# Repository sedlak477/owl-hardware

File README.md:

# OWL Hardware

Hardware design files for the OWL measurement tool.

The OWL is a rotating platform driven by a BLDC motor under field-oriented control.
Power and USB data are passed from the stationary base to the rotating part through a slip ring,
so devices mounted on top can be rotated continuously while staying connected to a host.

## Status

- **[v1.0.0](https://github.com/sedlak477/owl-hardware/releases/tag/v1.0.0)** is the OWL as built and tested. It works, with the known issues listed in its release notes:
  the 5V rail can oscillate when USB and the power supply are both connected (workaround: cut the controller's `VBUS` jumper JP1),
  the stator's data USB-C port only works in one cable orientation,
  the sensor's mounting holes are missing (drill them, 1.8 mm),
  the green LEDs are very bright,
  and the USB hub (IC1) has no pin-1 marker.
- **Releases after v1.0.0**, including the latest, should fix these issues, but no boards have been built from them yet, so they are **untested**.
  Other changes since the built boards: plated shell-tab holes for the controller's USB-C connector J3, a different part for the controller's `USER` LED D7, and no assembled parts on the controller's bottom side.
- The payload adapters and the tripod mount in [`payload/`](payload/README.md) use version 2 of the payload connector, which is incompatible with version 1. For an OWL with the version 1 connector, use [release v1.2.2](https://github.com/sedlak477/owl-hardware/tree/v1.2.2).
- The 5V oscillation is only worked around: JP1 now ships open, so the controller runs from the power supply only (see [Power supply](docs/Assembly%20instructions.md#power-supply)). A proper fix is planned for the next board revision.

## Building an OWL

1. Download the files from the [latest release](https://github.com/sedlak477/owl-hardware/releases/latest):
   - `owl-<version>-jlcpcb.zip`: everything needed to order the three assembled PCBs from JLCPCB
   - `owl-<version>-3d-print.zip`: the 3D-printed parts
   - `owl-<version>-generic.zip`: manufacturer-neutral PCB files and schematics, if you order elsewhere
2. Order the PCBs, see [pcb/README.md](pcb/README.md).
3. Print the parts, see [cad/README.md](cad/README.md).
4. Assemble the OWL and flash the firmware, see the [assembly instructions](docs/Assembly%20instructions.md).
5. Print an adapter for your payload, see [payload/README.md](payload/README.md).

## Architecture

- **Stator PCB**: Sits in the stationary base. Provides the USB-C power input with a USB PD trigger (CH224K) and the USB data port to the host.
- **Rotor PCB** (controller): Rotates with the platform. Contains the RP2354B controller, the DRV8311 BLDC driver, 5 V and 3.3 V regulators, a USB hub with a passthrough port for the payload, and a Qwiic (I²C) port.
- **Magnetic sensor PCB**: Measures the rotor angle for motor control using a magnetic angle sensor.

## Repository structure

| Path             | Content                                         |
| :--------------- | :---------------------------------------------- |
| `pcb/controller` | KiCad project for the rotor/controller PCB.     |
| `pcb/stator`     | KiCad project for the stator PCB.               |
| `pcb/sensor`     | KiCad projects for the magnetic sensor PCBs.    |
| `cad`            | Link to the Onshape document and 3D-print files.|
| `payload`        | Adapters for mounting payloads, and the payload interface. |
| `docs`           | Assembly instructions, renders, and diagrams.   |

Each PCB folder contains a `schematic.pdf`, the KiCad project in `src`, and production files in `production` (generic, and ready to upload to JLCPCB). See [pcb/README.md](pcb/README.md) for the stackups and how to order the boards.

## Editing the design

Requirements:

- [KiCad](https://www.kicad.org/) 10 or newer
- [Git LFS](https://git-lfs.com/) for STEP models, PDFs, images, and fabrication archives

```sh
git lfs install
git clone git@github.com:sedlak477/owl-hardware.git
```

After changing a board, regenerate its production files with `pcb/export-production.sh` (see [pcb/README.md](pcb/README.md#regenerating-the-production-files-only-after-changing-the-design)).
Pushing a tag starting with `v` (e.g. `v1.1.0`) creates a release with the packaged production and 3D-print files.

## Related resources

[owl-firmware](https://github.com/sedlak477/owl-firmware): The firmware for the OWL platform.  
[owl-ranger](https://github.com/sedlak477/owl-ranger): A script for stepping through some orientations and recording measurements.  
[pyowl](https://github.com/sedlak477/pyowl): A python library for interacting with the OWL.  
[Dataset](https://doi.org/10.3217/kh254-z8374): Orientation-diverse BLE Channel Sounding and UWB ranging measurements recorded with the OWL.

## License

Copyright 2026 Michael Sedlak. Licensed under [CERN-OHL-P-2.0](LICENSE), without any warranty.

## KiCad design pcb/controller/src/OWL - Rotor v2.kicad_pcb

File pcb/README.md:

# PCBs

| Board                         | Folder             | Layers | Size           | Thickness | Copper                    | Solder mask | Parts on    |
| :---------------------------- | :----------------- | :----- | :------------- | :-------- | :------------------------ | :---------- | :---------- |
| Rotor / controller            | `controller/`      | 4      | 60 x 60 mm     | 1.6 mm    | 1 oz outer, 0.5 oz inner  | Purple      | top only    |
| Stator                        | `stator/`          | 2      | 44 x 44 mm     | 1.6 mm    | 1 oz                      | Black       | both sides  |
| Magnetic sensor (MA600A)      | `sensor/ma600a/`   | 2      | 22.3 x 20 mm   | 1.6 mm    | 1 oz                      | Yellow      | both sides  |

ENIG surface finish is recommended.
Minimum track width and clearance are 0.15 mm, minimum drill is 0.25 mm (controller) or 0.3 mm (stator, sensor).

Each board folder contains:

| Path                  | Content                                                                          |
| :-------------------- | :------------------------------------------------------------------------------- |
| `schematic.pdf`       | Schematic.                                                                       |
| `src/`                | KiCad project and STEP model of the assembled board.                             |
| `production/generic/` | Files for any manufacturer (see below).                                          |
| `production/jlcpcb/`  | Files ready to upload to JLCPCB for fabrication and assembly.                    |

The easiest way to get the files is the [latest release](https://github.com/sedlak477/owl-hardware/releases/latest): `owl-<version>-jlcpcb.zip` has the JLCPCB files and `owl-<version>-generic.zip` the generic files and schematics, each with one folder per board.

## Ordering from JLCPCB

> [!WARNING]
> **Check the rotation of every part in JLCPCB's placement preview before you order.**
> JLCPCB's part models don't always line up with the footprints, so some parts can show up rotated (often by 90° or 180°) or shifted.
> JLCPCB assembles the board as the preview shows it: a wrongly rotated IC, LED or connector is soldered on the wrong way round, and the board has to be reworked or thrown away.
> See step 5 below.

Order each board (`controller`, `stator`, `sensor-ma600a`) separately. Download and unzip `owl-<version>-jlcpcb.zip`, then for each board:

1. Go to [jlcpcb.com](https://jlcpcb.com), click *Order now*, and upload `<board>/<board>-gerbers.zip`. Don't unzip it, JLCPCB wants the zip.
2. Check that layers, size and thickness match the table above, and pick the solder mask color you like.
3. Enable *PCB Assembly*. The controller is assembled on the top side only; the stator and the sensor have parts on both sides, so select assembly on both sides for them.
4. Upload `<board>/<board>-bom.csv` as the BOM and `<board>/<board>-positions.csv` as the CPL (pick-and-place) file.
5. Check the part matching, then go through **every part** in the placement preview and check both its position and its rotation:
   - Position: its pins sit on their pads.
   - Rotation of ICs: the pin-1 marker on the part (dot, notch or bevel) sits at the pin-1 marker on the silkscreen.
   - Rotation of LEDs: the cathode sits at the cathode marker on the silkscreen.
   - Rotation of connectors: the part matches its silkscreen outline, with the opening on the correct side.

   Rotate or move any part that is off directly in the preview before ordering. Resistors and ceramic capacitors are not polarized, so for them a 180° rotation does not matter.

On the controller, the optional RM2 radio module (U6) and microSD socket (J8) are marked DNP and are not assembled, and neither are their support parts on the bottom side (C43, C44, R1, R2). Solder them by hand if you need them; their values and part numbers are in the schematic.

## Ordering elsewhere

`owl-<version>-generic.zip` (or `production/generic/` in each board folder) contains manufacturer-neutral files, plus each board's schematic:

| File                      | Content                                                                                       |
| :------------------------ | :-------------------------------------------------------------------------------------------- |
| `<board>-gerbers.zip`     | Gerber X2 layers, Excellon drill files (plated and non-plated separate), and a Gerber job file with the stackup. |
| `<board>-netlist.ipc`     | IPC-D-356 netlist for electrical testing.                                                     |
| `<board>-bom.csv`         | BOM with manufacturer and manufacturer part number (MPN), plus the LCSC number where available. |
| `<board>-positions.csv`   | Pick-and-place file as exported by KiCad (mm, rotation in KiCad convention, both sides).      |

The Gerbers work at any PCB manufacturer.
Assembly houses usually want the BOM and position files in their own format; the columns in the generic files map directly to theirs.
Rotation conventions differ between assembly houses, so **check the rotation of every polarized part in their placement preview**, the same way as for JLCPCB (step 5 above).
The JLCPCB position file is not generic: it contains JLCPCB-specific rotation and offset corrections.

## Regenerating the production files (only after changing the design)

Not needed for ordering boards: the production files in each release are ready to use.

Run `pcb/export-production.sh` (or `pcb/export-production.sh <board>` for one board: `controller`, `stator`, `sensor-ma600a`).
It needs `kicad-cli` (KiCad 10) and, for the JLCPCB files, the [Fabrication Toolkit](https://github.com/bennymeg/Fabrication-Toolkit) KiCad plugin.
Set `KICAD_PYTHON` to the Python interpreter KiCad uses if it is not the default `python3`, and `FABRICATION_TOOLKIT_DIR` if the plugin is not installed in `~/.local/share/kicad/10.0/3rdparty/plugins`.

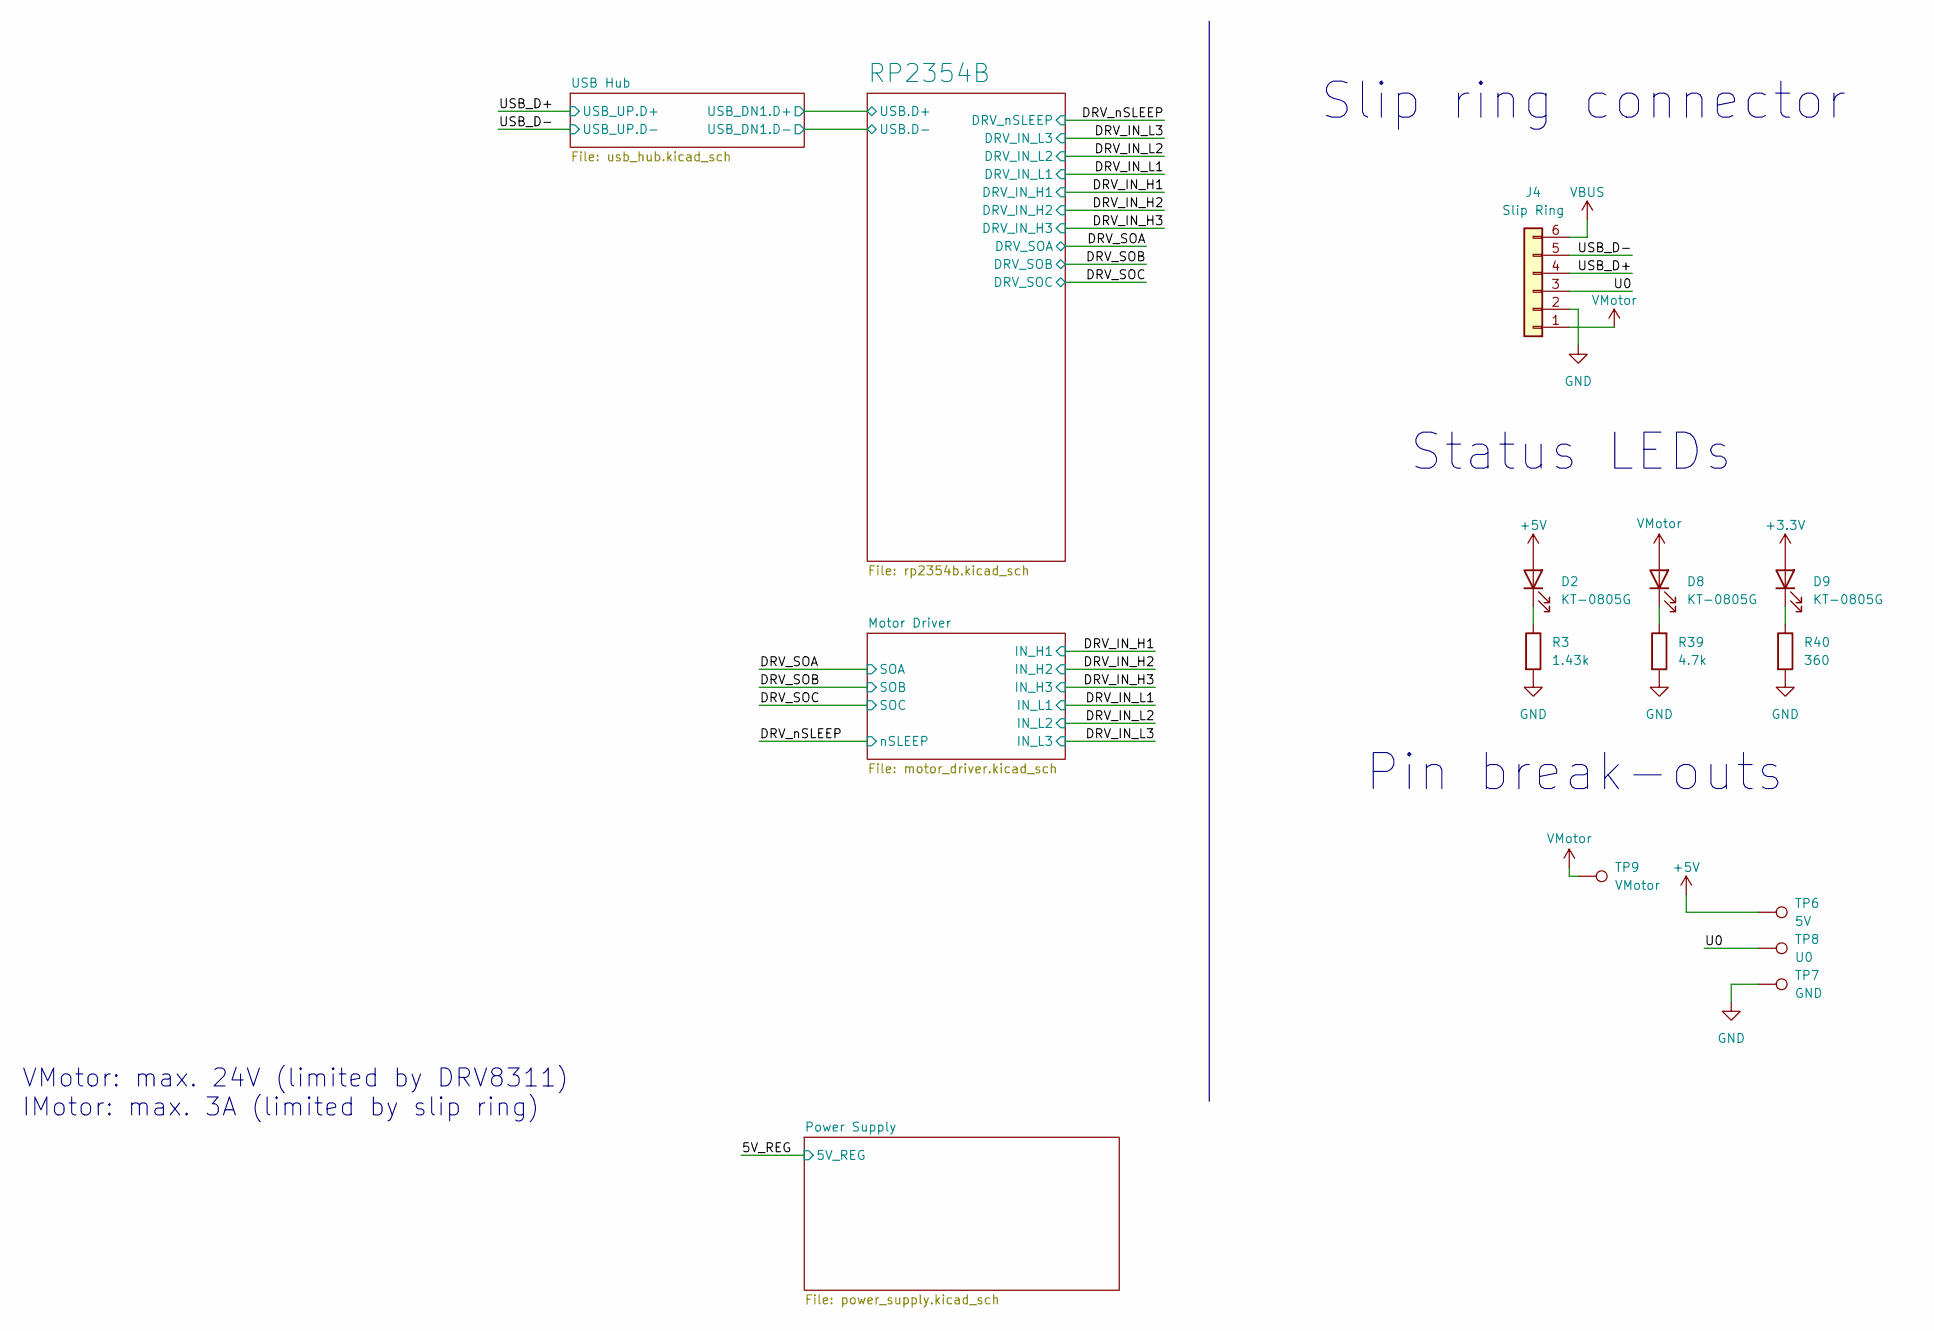
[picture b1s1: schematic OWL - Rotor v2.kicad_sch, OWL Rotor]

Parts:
D2, D8, D9: KT-0805G; LED_0805_2012Metric; MPN KT-0805G; LCSC C2297
J4: Slip Ring; CONN_BM06B-PASS-1_JST; MPN BM06B-PASS-TFT(LF)(SN); LCSC C265376
R3: 1.43k; R_0402_1005Metric; MPN RC0402FR-071K43L; LCSC C163483
R39: 4.7k; R_0402_1005Metric; MPN 0402WGF4701TCE; LCSC C25900
R40: 360; R_0402_1005Metric; MPN FRC0402F3600TS; LCSC C2930003
TP6: 5V; TestPoint_Pad_D1.0mm
TP7: GND; TestPoint_Pad_D1.0mm
TP8: U0; TestPoint_Pad_D1.0mm
TP9: VMotor; TestPoint_Pad_D1.0mm

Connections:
+3.3V: D9.2 (A); also elsewhere on the board
+5V: D2.2 (A), TP6.1; also elsewhere on the board
/U0: J4.3, TP8.1
/USB_D+: J4.4; also elsewhere on the board
/USB_D-: J4.5; also elsewhere on the board
GND: J4.2, R3.2, R39.2, R40.2, TP7.1; also elsewhere on the board
unnamed: D2.1 (K), R3.1
unnamed: D8.1 (K), R39.1
unnamed: D9.1 (K), R40.1
VBUS: J4.6; also elsewhere on the board
VMotor: D8.2 (A), J4.1, TP9.1; also elsewhere on the board

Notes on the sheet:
VMotor: max. 24V (limited by DRV8311) IMotor: max. 3A (limited by slip ring)
Status LEDs
Slip ring connector
Pin break-outs

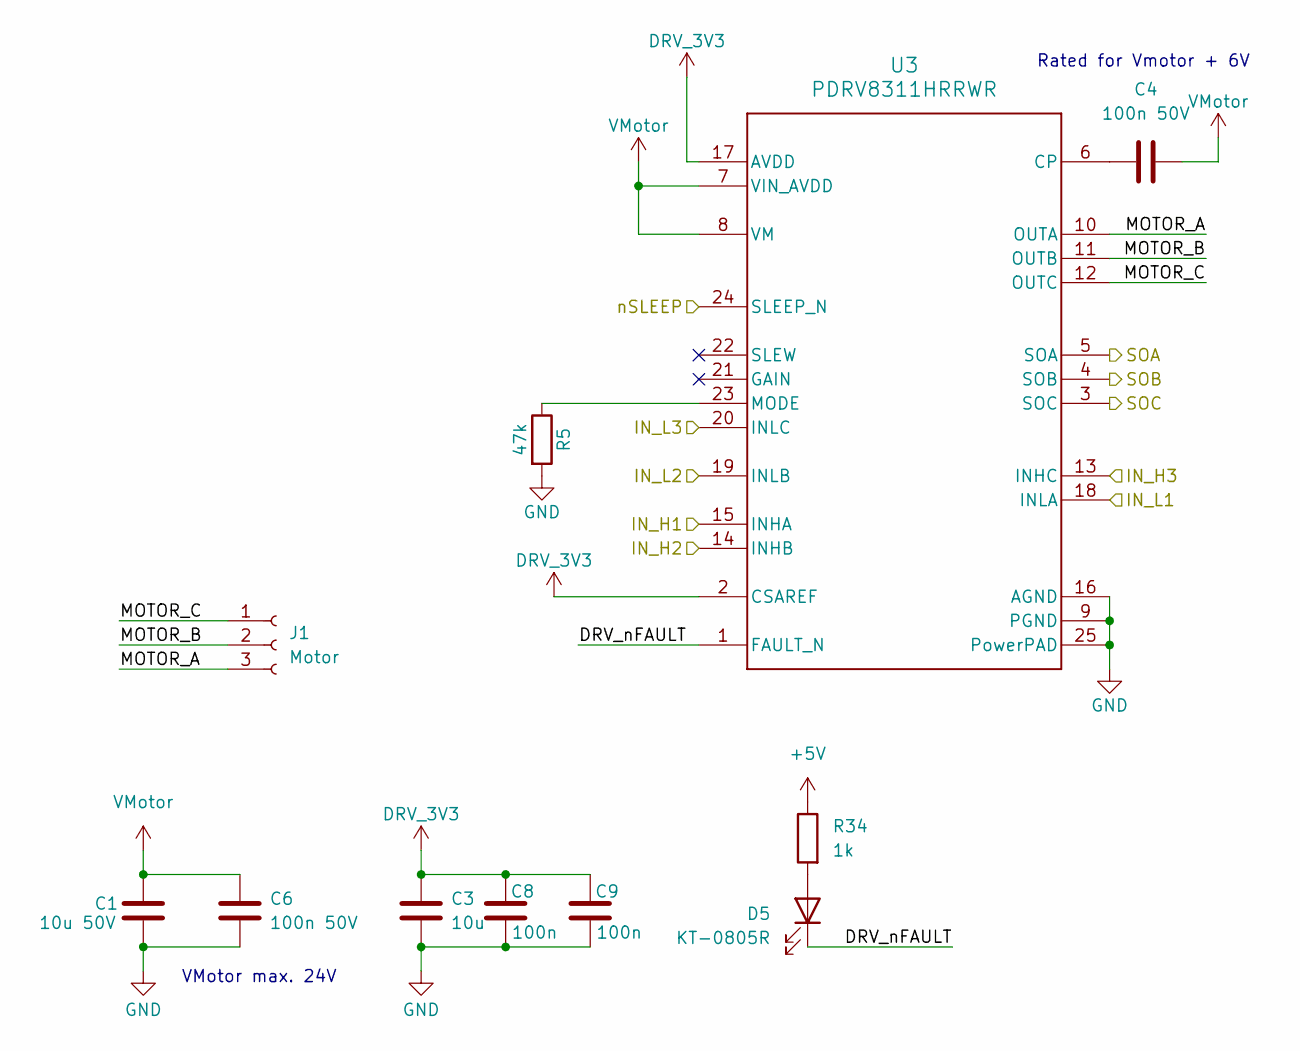
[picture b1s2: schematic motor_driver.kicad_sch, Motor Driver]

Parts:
C1: 10u 50V; C_0805_2012Metric; MPN GRM21BR61H106KE43L; LCSC C440198
C3: 10u; C_0603_1608Metric; MPN CL10A106KP8NNNC; LCSC C19702
C4, C6: 100n 50V; C_0402_1005Metric; MPN CL05B104KB54PNC; LCSC C307331
C8, C9: 100n; C_0402_1005Metric; MPN CL05B104KO5NNNC; LCSC C1525
D5: KT-0805R; LED_0805_2012Metric; MPN NCD0805R1; LCSC C84256
J1: Motor; Molex_PicoBlade_53261-0371_1x03-1MP_P1.25mm_Horizontal; MPN 532610371; LCSC C293630
R5: 47k; R_0402_1005Metric; MPN 0402WGF4702TCE; LCSC C25792
R34: 1k; R_0402_1005Metric; MPN 0402WGF1001TCE; LCSC C11702
U3: PDRV8311HRRWR; RRW0024-MFG; MPN DRV8311HRRWR; LCSC C5218862

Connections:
+5V: R34.1; also elsewhere on the board
/DRV_IN_H1: U3.15 (INHA); also elsewhere on the board
/DRV_IN_H2: U3.14 (INHB); also elsewhere on the board
/DRV_IN_H3: U3.13 (INHC); also elsewhere on the board
/DRV_IN_L1: U3.18 (INLA); also elsewhere on the board
/DRV_IN_L2: U3.19 (INLB); also elsewhere on the board
/DRV_IN_L3: U3.20 (INLC); also elsewhere on the board
/DRV_SOA: U3.5 (SOA); also elsewhere on the board
/DRV_SOB: U3.4 (SOB); also elsewhere on the board
/DRV_SOC: U3.3 (SOC); also elsewhere on the board
/DRV_nSLEEP: U3.24 (SLEEP_N); also elsewhere on the board
/Motor Driver/DRV_nFAULT: D5.1 (K), U3.1 (FAULT_N)
/Motor Driver/MOTOR_A: J1.3, U3.10 (OUTA)
/Motor Driver/MOTOR_B: J1.2, U3.11 (OUTB)
/Motor Driver/MOTOR_C: J1.1, U3.12 (OUTC)
DRV_3V3: C3.1, C8.2, C9.2, U3.2 (CSAREF), U3.17 (AVDD)
GND: C1.2, C3.2, C6.2, C8.1, C9.1, R5.2, U3.9 (PGND), U3.16 (AGND), U3.25 (PowerPAD); also elsewhere on the board
unnamed: D5.2 (A), R34.2
unnamed: C4.1, U3.6 (CP)
unnamed: R5.1, U3.23 (MODE)
VMotor: C1.1, C4.2, C6.1, U3.7 (VIN_AVDD), U3.8 (VM); also elsewhere on the board

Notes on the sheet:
Rated for Vmotor + 6V
VMotor max. 24V

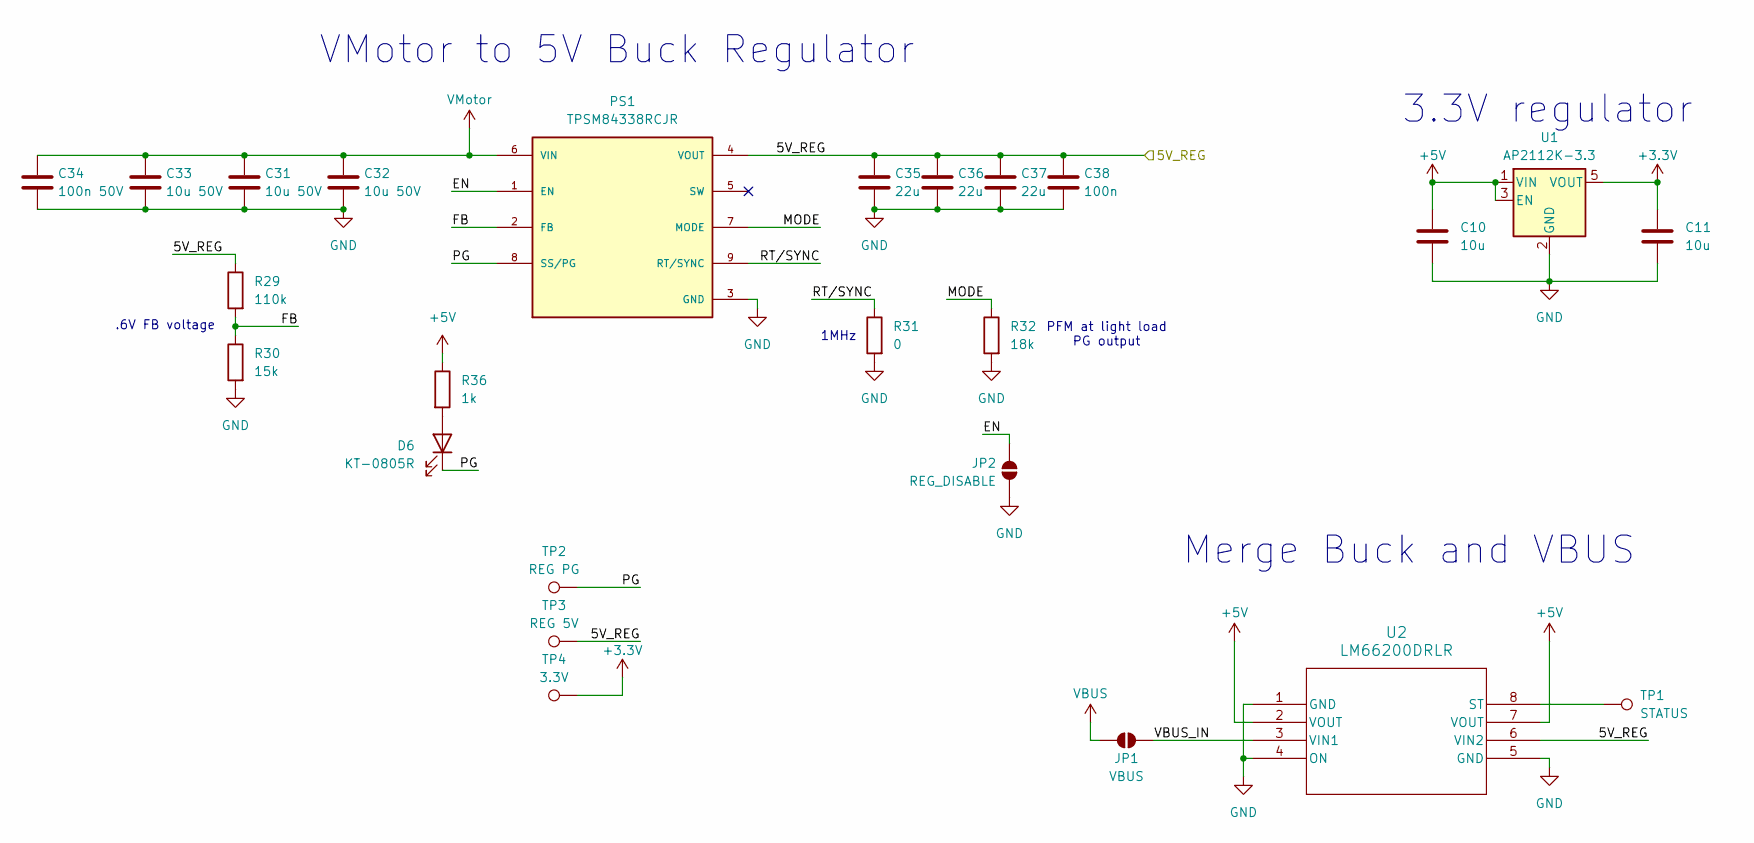
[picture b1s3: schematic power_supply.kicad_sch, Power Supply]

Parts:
C10, C11: 10u; C_0603_1608Metric; MPN CL10A106KP8NNNC; LCSC C19702
C31, C32, C33: 10u 50V; C_0805_2012Metric; MPN GRM21BR61H106KE43L; LCSC C440198
C34: 100n 50V; C_0402_1005Metric; MPN CL05B104KB54PNC; LCSC C307331
C35, C36, C37: 22u; C_0603_1608Metric; MPN 0603X226M100NT; LCSC C60077
C38: 100n; C_0402_1005Metric; MPN CL05B104KO5NNNC; LCSC C1525
D6: KT-0805R; LED_0805_2012Metric; MPN NCD0805R1; LCSC C84256
JP1: VBUS; SolderJumper-2_P1.3mm_Open_RoundedPad1.0x1.5mm
JP2: REG_DISABLE; SolderJumper-2_P1.3mm_Open_RoundedPad1.0x1.5mm
PS1: TPSM84338RCJR; CONV_TPSM84338RCJR; PARTREV November 2024; LCSC C47122151
R29: 110k; R_0402_1005Metric; MPN RC0402FR-07110KL; LCSC C138065
R30: 15k; R_0402_1005Metric; MPN 0402WGF1502TCE; LCSC C25756
R31: 0; R_0402_1005Metric; MPN 0402WGF0000TCE; LCSC C17168
R32: 18k; R_0402_1005Metric; MPN 0402WGF1802TCE; LCSC C25762
R36: 1k; R_0402_1005Metric; MPN 0402WGF1001TCE; LCSC C11702
TP1: STATUS; TestPoint_Pad_D1.0mm
TP2: REG PG; TestPoint_Pad_D1.0mm
TP3: REG 5V; TestPoint_Pad_D1.0mm
TP4: 3.3V; TestPoint_Pad_D1.0mm
U1: AP2112K-3.3; SOT-23-5; MPN AP2112K-3.3TRG1; LCSC C23380830
U2: LM66200DRLR; SOT-5X3_DRL_TEX; MPN LM66200DRLR; LCSC C3235556

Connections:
+3.3V: C11.1, TP4.1, U1.5 (VOUT); also elsewhere on the board
+5V: C10.1, R36.1, U1.1 (VIN), U1.3 (EN), U2.2 (VOUT), U2.7 (VOUT); also elsewhere on the board
/5V_REG: C35.1, C36.1, C37.1, C38.1, PS1.4 (VOUT), R29.1, TP3.1, U2.6 (VIN2)
/Power Supply/EN: JP2.2 (B), PS1.1 (EN)
/Power Supply/FB: PS1.2 (FB), R29.2, R30.1
/Power Supply/MODE: PS1.7 (MODE), R32.1
/Power Supply/PG: D6.1 (K), PS1.8 (SS/PG), TP2.1
/Power Supply/RT/SYNC: PS1.9 (RT/SYNC), R31.1
/Power Supply/VBUS_IN: JP1.1 (A), U2.3 (VIN1)
GND: C10.2, C11.2, C31.2, C32.2, C33.2, C34.2, C35.2, C36.2, C37.2, C38.2, JP2.1 (A), PS1.3 (GND), R30.2, R31.2, R32.2, U1.2 (GND), U2.1 (GND), U2.4 (ON), U2.5 (GND); also elsewhere on the board
unnamed: D6.2 (A), R36.2
unnamed: TP1.1, U2.8 (ST)
VBUS: JP1.2 (B); also elsewhere on the board
VMotor: C31.1, C32.1, C33.1, C34.1, PS1.6 (VIN); also elsewhere on the board

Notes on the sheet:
1MHz
VMotor to 5V Buck Regulator
Merge Buck and VBUS
.6V FB voltage
3.3V regulator
PFM at light load PG output

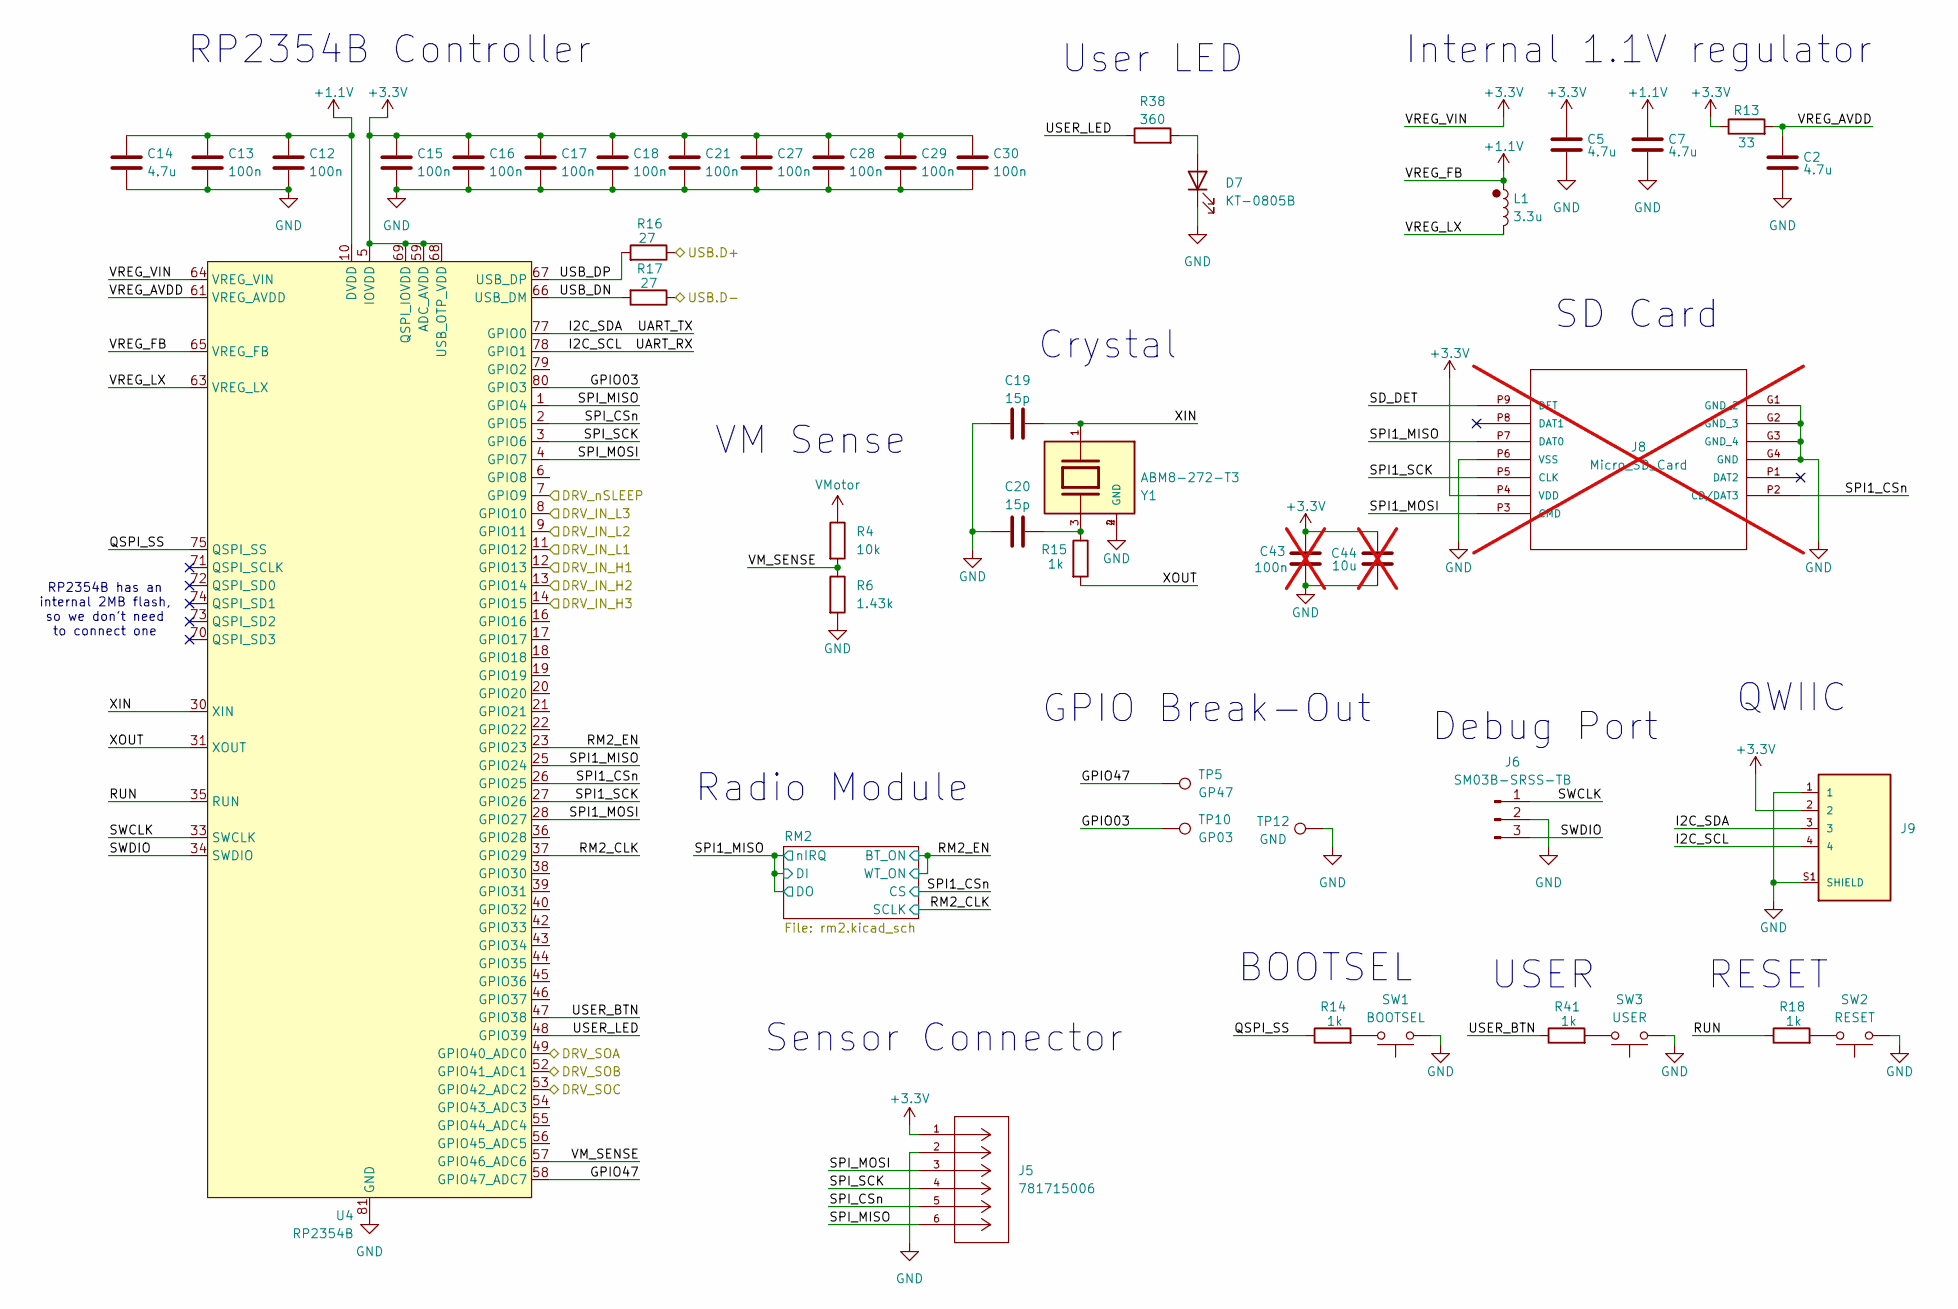
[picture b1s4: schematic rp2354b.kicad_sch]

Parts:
C2, C14: 4.7u; C_0402_1005Metric; MPN CL05A475MP5NRNC; LCSC C23733
C5, C7: 4.7u; C_0402_1005Metric_small_pads; MPN CL05A475MP5NRNC; LCSC C23733
C12, C13, C15, C16, C17, C18, C21, C27, C28, C29, C30: 100n; C_0402_1005Metric; MPN CL05B104KO5NNNC; LCSC C1525
C19, C20: 15p; C_0402_1005Metric; MPN 0402CG150J500NT; LCSC C1548
C43: 100n; C_0402_1005Metric; MPN CL05B104KO5NNNC; LCSC C1525; not fitted
C44: 10u; C_0603_1608Metric; MPN CL10A106KP8NNNC; LCSC C19702; not fitted
D7: KT-0805B; LED_0805_2012Metric; MPN KT-0805B; LCSC C2293
J5: 781715006; CONN06_781715006_MOL; MPN 781715006; LCSC C107412
J6: SM03B-SRSS-TB; JST_SH_SM03B-SRSS-TB_1x03-1MP_P1.00mm_Horizontal; MPN SM03B-SRSS-TB(LF)(SN); LCSC C160403
J8: Micro_SD_Card; 105162-0001_MOL; PARTREV 0; LCSC C3177046; not fitted
J9: SM04B-SRSS-TB_LF__SN_; JST_SM04B-SRSS-TB_LF__SN_; MPN SM04B-SRSS-TB(LF)(SN); LCSC C160404
L1: 3.3u; AOTAB201610S3R3101T; MPN AOTA-B201610S3R3-101-T; LCSC C42411119
R4: 10k; R_0402_1005Metric; MPN 0402WGF1002TCE; LCSC C25744
R6: 1.43k; R_0402_1005Metric; MPN RC0402FR-071K43L; LCSC C163483
R13: 33; R_0402_1005Metric; MPN 0402WGF330JTCE; LCSC C25105
R14, R15, R18, R41: 1k; R_0402_1005Metric; MPN 0402WGF1001TCE; LCSC C11702
R16, R17: 27; R_0402_1005Metric; MPN RC0402FR-0727RL; LCSC C138021
R38: 360; R_0402_1005Metric; MPN FRC0402F3600TS; LCSC C2930003
SW1: BOOTSEL; SW_SPST_B3U-1000P; MPN GT-TC032A-H015-L1; LCSC C843684
SW2: RESET; SW_SPST_B3U-1000P; MPN GT-TC032A-H015-L1; LCSC C843684
SW3: USER; SW_SPST_B3U-1000P; MPN GT-TC032A-H015-L1; LCSC C843684
TP5: GP47; TestPoint_Pad_D1.0mm
TP10: GP03; TestPoint_Pad_D1.0mm
TP12: GND; TestPoint_Pad_D1.0mm
U4: RP2354B; QFN-80-1EP_10x10mm_P0.4mm_EP3.4x3.4mm_ThermalVias; MPN RP2354B; LCSC C39843328
Y1: ABM8-272-T3; XTAL_ABM8-272-T3; PARTREV 07-29-20; LCSC C20625731

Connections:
+1.1V: C7.1, C12.1, C13.1, C14.1, L1.1, U4.10 (DVDD), U4.32 (DVDD), U4.51 (DVDD), U4.65 (VREG_FB)
+3.3V: C5.1, C15.1, C16.1, C17.1, C18.1, C21.1, C27.1, C28.1, C29.1, C30.1, C43.1, C44.1, J5.1, J8.P4 (VDD), J9.2, R13.1, U4.5 (IOVDD), U4.15 (IOVDD), U4.24 (IOVDD), U4.29 (IOVDD), U4.41 (IOVDD), U4.50 (IOVDD), U4.59 (ADC_AVDD), U4.60 (IOVDD), U4.64 (VREG_VIN), U4.68 (USB_OTP_VDD), U4.69 (QSPI_IOVDD), U4.76 (IOVDD); also elsewhere on the board
/DRV_IN_H1: U4.12 (GPIO13); also elsewhere on the board
/DRV_IN_H2: U4.13 (GPIO14); also elsewhere on the board
/DRV_IN_H3: U4.14 (GPIO15); also elsewhere on the board
/DRV_IN_L1: U4.11 (GPIO12); also elsewhere on the board
/DRV_IN_L2: U4.9 (GPIO11); also elsewhere on the board
/DRV_IN_L3: U4.8 (GPIO10); also elsewhere on the board
/DRV_SOA: U4.49 (GPIO40_ADC0); also elsewhere on the board
/DRV_SOB: U4.52 (GPIO41_ADC1); also elsewhere on the board
/DRV_SOC: U4.53 (GPIO42_ADC2); also elsewhere on the board
/DRV_nSLEEP: U4.7 (GPIO9); also elsewhere on the board
/RP2354B/GPIO03: TP10.1, U4.80 (GPIO3)
/RP2354B/GPIO47: TP5.1, U4.58 (GPIO47_ADC7)
/RP2354B/I2C_SCL: J9.4, U4.78 (GPIO1)
/RP2354B/I2C_SDA: J9.3, U4.77 (GPIO0)
/RP2354B/QSPI_SS: R14.1, U4.75 (QSPI_SS)
/RP2354B/RM2_CLK: U4.37 (GPIO29); also elsewhere on the board
/RP2354B/RM2_EN: U4.23 (GPIO23); also elsewhere on the board
/RP2354B/RUN: R18.1, U4.35 (RUN)
/RP2354B/SD_DET: J8.P9 (DET)
/RP2354B/SPI1_CSn: J8.P2 (CD/DAT3), U4.26 (GPIO25); also elsewhere on the board
/RP2354B/SPI1_MISO: J8.P7 (DAT0), U4.25 (GPIO24); also elsewhere on the board
/RP2354B/SPI1_MOSI: J8.P3 (CMD), U4.28 (GPIO27)
/RP2354B/SPI1_SCK: J8.P5 (CLK), U4.27 (GPIO26)
/RP2354B/SPI_CSn: J5.5, U4.2 (GPIO5)
/RP2354B/SPI_MISO: J5.6, U4.1 (GPIO4)
/RP2354B/SPI_MOSI: J5.3, U4.4 (GPIO7)
/RP2354B/SPI_SCK: J5.4, U4.3 (GPIO6)
/RP2354B/SWCLK: J6.1, U4.33 (SWCLK)
/RP2354B/SWDIO: J6.3, U4.34 (SWDIO)
/RP2354B/USB.D+: R16.1; also elsewhere on the board
/RP2354B/USB.D-: R17.1; also elsewhere on the board
/RP2354B/USB_DN: R17.2, U4.66 (USB_DM)
/RP2354B/USB_DP: R16.2, U4.67 (USB_DP)
/RP2354B/USER_BTN: R41.1, U4.47 (GPIO38)
/RP2354B/USER_LED: R38.1, U4.48 (GPIO39)
/RP2354B/VM_SENSE: R4.2, R6.1, U4.57 (GPIO46_ADC6)
/RP2354B/VREG_AVDD: C2.1, R13.2, U4.61 (VREG_AVDD)
/RP2354B/VREG_LX: L1.2, U4.63 (VREG_LX)
/RP2354B/XIN: C19.2, U4.30 (XIN), Y1.1
/RP2354B/XOUT: R15.2, U4.31 (XOUT)
GND: C2.2, C5.2, C7.2, C12.2, C13.2, C14.2, C15.2, C16.2, C17.2, C18.2, C19.1, C20.1, C21.2, C27.2, C28.2, C29.2, C30.2, C43.2, C44.2, D7.1 (K), J5.2, J6.2, J8.G1 (GND_2), J8.G2 (GND_3), J8.G3 (GND_4), J8.G4 (GND), J8.P6 (VSS), J9.1, J9.S1 (SHIELD), J9.S2 (SHIELD), R6.2, SW1.1, SW2.1, SW3.1, TP12.1, U4.62 (VREG_PGND), U4.81 (GND), Y1.2 (GND), Y1.4 (GND); also elsewhere on the board
unnamed: C20.2, R15.1, Y1.3
unnamed: D7.2 (A), R38.2
unnamed: R14.2, SW1.2
unnamed: R18.2, SW2.2
unnamed: R41.2, SW3.2
VMotor: R4.1; also elsewhere on the board

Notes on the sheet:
User LED
USER
Sensor Connector
VM Sense
Internal 1.1V regulator
BOOTSEL
Radio Module
QWIIC
Crystal
SD Card
RP2354B has an internal 2MB flash, so we don't need to connect one
GPIO Break-Out
RP2354B Controller
RESET
Debug Port

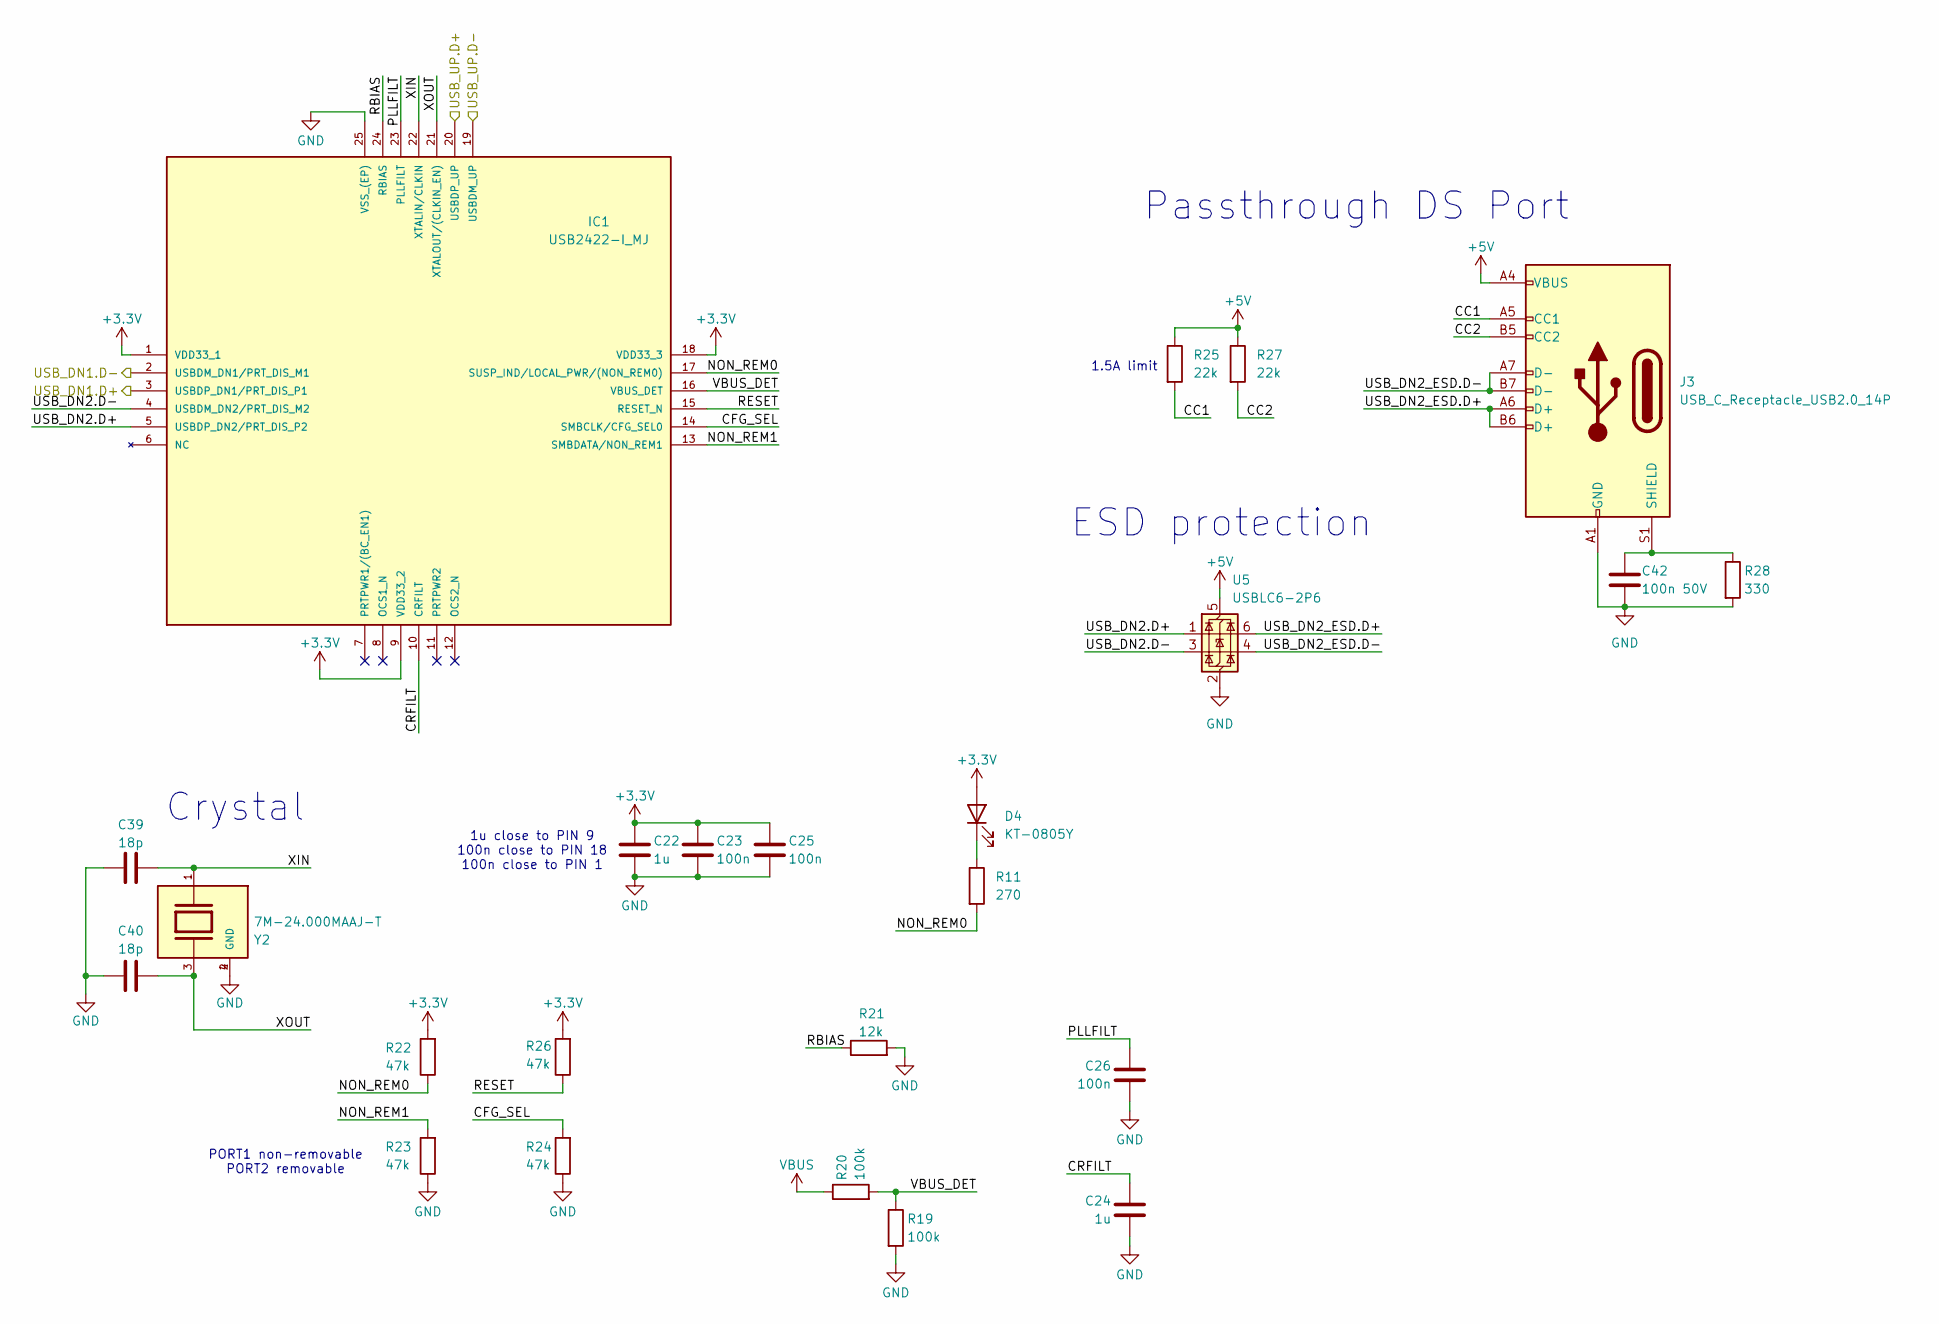
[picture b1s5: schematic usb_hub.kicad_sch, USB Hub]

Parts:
C22, C24: 1u; C_0402_1005Metric; MPN CL05A105KA5NQNC; LCSC C52923
C23, C25, C26: 100n; C_0402_1005Metric; MPN CL05B104KO5NNNC; LCSC C1525
C39, C40: 18p; C_0402_1005Metric; MPN 0402CG180J500NT; LCSC C1549
C42: 100n 50V; C_0402_1005Metric; MPN GRM155R71H104KE14D; LCSC C77020
D4: KT-0805Y; LED_0805_2012Metric; MPN KT-0805Y; LCSC C2296
IC1: USB2422-I_MJ; QFN50P400X400X100-25N; MOUSER_PART_NUMBER 579-USB2422-I/MJ
J3: USB_C_Receptacle_USB2.0_14P; USB_C_Receptacle_GCT_USB4105-xx-A_16P_TopMnt_Horizontal; MPN USB4105-GF-A-060; LCSC C3025063
R11: 270; R_0402_1005Metric; MPN RC0402FR-07270RL; LCSC C163474
R19, R20: 100k; R_0402_1005Metric; MPN 0402WGF1003TCE; LCSC C25741
R21: 12k; R_0402_1005Metric; MPN 0402WGF1202TCE; LCSC C25752
R22, R23, R24, R26: 47k; R_0402_1005Metric; MPN 0402WGF4702TCE; LCSC C25792
R25, R27: 22k; R_0402_1005Metric; MPN 0402WGF2202TCE; LCSC C25768
R28: 330; R_0402_1005Metric; MPN 0402WGF3300TCE; LCSC C25104
U5: USBLC6-2P6; SOT-666; MPN USBLC6-2P6; LCSC C2827693
Y2: 7M-24.000MAAJ-T; 7M24000MAAJT; PARTREV 07-29-20; LCSC C2450233

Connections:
+3.3V: C22.1, C23.1, C25.1, D4.2 (A), IC1.1 (VDD33_1), IC1.9 (VDD33_2), IC1.18 (VDD33_3), R22.2, R26.2; also elsewhere on the board
+5V: J3.A4 (VBUS), J3.A9 (VBUS), J3.B4 (VBUS), J3.B9 (VBUS), R25.1, R27.1, U5.5 (VBUS); also elsewhere on the board
/RP2354B/USB.D+: IC1.3 (USBDP_DN1/PRT_DIS_P1); also elsewhere on the board
/RP2354B/USB.D-: IC1.2 (USBDM_DN1/PRT_DIS_M1); also elsewhere on the board
/USB Hub/CC1: J3.A5 (CC1), R25.2
/USB Hub/CC2: J3.B5 (CC2), R27.2
/USB Hub/CFG_SEL: IC1.14 (SMBCLK/CFG_SEL0), R24.2
/USB Hub/CRFILT: C24.1, IC1.10 (CRFILT)
/USB Hub/NON_REM0: IC1.17 (SUSP_IND/LOCAL_PWR/(NON_REM0)), R11.2, R22.1
/USB Hub/NON_REM1: IC1.13 (SMBDATA/NON_REM1), R23.2
/USB Hub/PLLFILT: C26.1, IC1.23 (PLLFILT)
/USB Hub/RBIAS: IC1.24 (RBIAS), R21.1
/USB Hub/RESET: IC1.15 (RESET_N), R26.1
/USB Hub/USB_DN2.D+: IC1.5 (USBDP_DN2/PRT_DIS_P2), U5.1 (I/O1)
/USB Hub/USB_DN2.D-: IC1.4 (USBDM_DN2/PRT_DIS_M2), U5.3 (I/O2)
/USB Hub/USB_DN2_ESD.D+: J3.A6 (D+), J3.B6 (D+), U5.6 (I/O1)
/USB Hub/USB_DN2_ESD.D-: J3.A7 (D-), J3.B7 (D-), U5.4 (I/O2)
/USB Hub/VBUS_DET: IC1.16 (VBUS_DET), R19.1, R20.2
/USB Hub/XIN: C39.2, IC1.22 (XTALIN/CLKIN), Y2.1
/USB Hub/XOUT: C40.2, IC1.21 (XTALOUT/(CLKIN_EN)), Y2.3
/USB_D+: IC1.20 (USBDP_UP); also elsewhere on the board
/USB_D-: IC1.19 (USBDM_UP); also elsewhere on the board
GND: C22.2, C23.2, C24.2, C25.2, C26.2, C39.1, C40.1, C42.2, IC1.25 (VSS_(EP)), J3.A1 (GND), J3.A12 (GND), J3.B1 (GND), J3.B12 (GND), R19.2, R21.2, R23.1, R24.1, R28.2, U5.2 (GND), Y2.2 (GND), Y2.4 (GND); also elsewhere on the board
unnamed: D4.1 (K), R11.1
unnamed: C42.1, J3.S1 (SHIELD), R28.1
VBUS: R20.1; also elsewhere on the board

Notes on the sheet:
PORT1 non-removable PORT2 removable
1.5A limit
ESD protection
1u close to PIN 9 100n close to PIN 18 100n close to PIN 1
Passthrough DS Port
Crystal

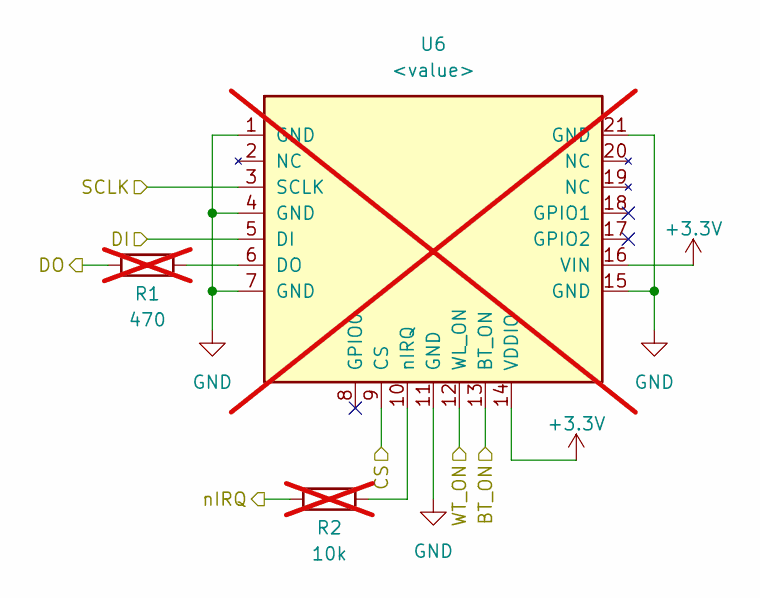
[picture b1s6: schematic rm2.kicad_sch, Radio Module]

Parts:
R1: 470; R_0402_1005Metric; MPN 0402WGF4700TCE; LCSC C25117; not fitted
R2: 10k; R_0402_1005Metric; MPN 0402WGF1002TCE; LCSC C25744; not fitted
U6: <value>; rpi_rmc20452t; not fitted

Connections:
+3.3V: U6.14 (VDDIO), U6.16 (VIN); also elsewhere on the board
/RP2354B/RM2_CLK: U6.3 (SCLK); also elsewhere on the board
/RP2354B/RM2_EN: U6.12 (WL_ON), U6.13 (BT_ON); also elsewhere on the board
/RP2354B/SPI1_CSn: U6.9 (CS); also elsewhere on the board
/RP2354B/SPI1_MISO: R1.2, R2.2, U6.5 (DI); also elsewhere on the board
GND: U6.1 (GND), U6.4 (GND), U6.7 (GND), U6.11 (GND), U6.15 (GND), U6.21 (GND); also elsewhere on the board
unnamed: R1.1, U6.6 (DO)
unnamed: R2.1, U6.10 (nIRQ)
